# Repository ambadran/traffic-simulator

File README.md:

# traffic-simulator

This Project is a real-life simulation of a traffic camera monitoring for speed, traffic light passing and other violations. Incorporating IOT with a Web App hosting to monitor and control everything.

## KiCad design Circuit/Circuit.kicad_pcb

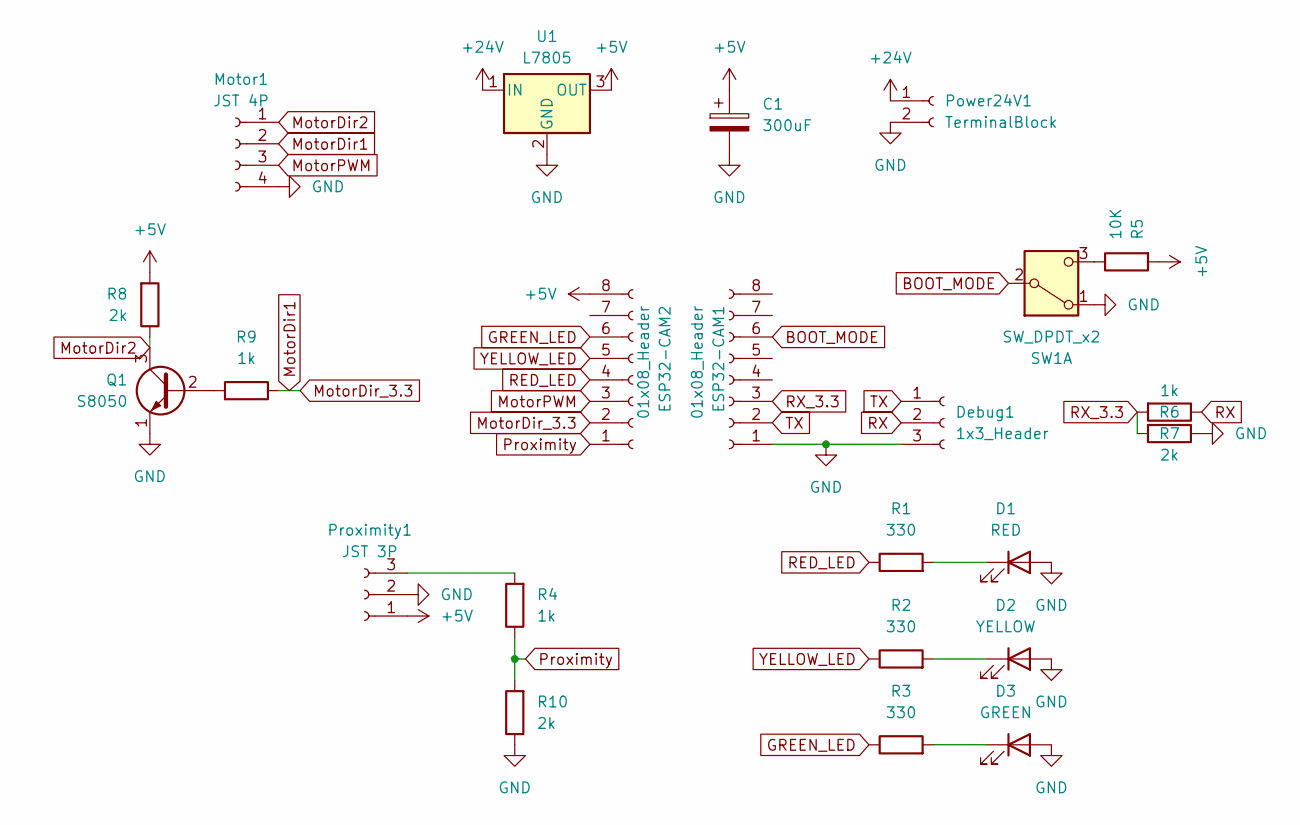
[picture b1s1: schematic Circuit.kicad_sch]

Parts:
C1: 300uF; CP_Radial_D8.0mm_P3.80mm
D1: RED; JST_EH_B2B-EH-A_1x02_P2.50mm_Vertical
D2: YELLOW; JST_EH_B2B-EH-A_1x02_P2.50mm_Vertical
D3: GREEN; JST_EH_B2B-EH-A_1x02_P2.50mm_Vertical
Debug1: 1x3_Header; PinSocket_1x03_P2.54mm_Vertical
ESP32-CAM1, ESP32-CAM2: 01x08_Header; PinSocket_1x08_P2.54mm_Vertical
Motor1: JST 4P; JST_EH_B4B-EH-A_1x04_P2.50mm_Vertical
Power24V1: TerminalBlock; TerminalBlock_bornier-2_P5.08mm
Proximity1: JST 3P; JST_EH_B3B-EH-A_1x03_P2.50mm_Vertical
Q1: S8050; TO-92_Inline_Wide
R1, R2, R3: 330; R_Axial_DIN0207_L6.3mm_D2.5mm_P7.62mm_Horizontal
R4, R6, R9: 1k; R_Axial_DIN0207_L6.3mm_D2.5mm_P7.62mm_Horizontal
R5: 10K; R_Axial_DIN0207_L6.3mm_D2.5mm_P7.62mm_Horizontal
R7, R8, R10: 2k; R_Axial_DIN0207_L6.3mm_D2.5mm_P7.62mm_Horizontal
SW1: SW_DPDT_x2; PinSocket_1x03_P2.54mm_Vertical
U1: L7805; TO-220-3_Vertical

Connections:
+5V: C1.1, ESP32-CAM2.8, Proximity1.1, R5.2, R8.2, U1.3 (OUT)
+24V: Power24V1.1, U1.1 (IN)
BOOT_MODE: ESP32-CAM1.6, SW1.2 (B)
GND: C1.2, D1.2 (A), D2.2 (A), D3.2 (A), Debug1.3, ESP32-CAM1.1, Motor1.4, Power24V1.2, Proximity1.2, Q1.1 (E), R7.1, R10.1, SW1.1 (A), U1.2 (GND)
GREEN_LED: ESP32-CAM2.6, R3.1
MotorDir1: ESP32-CAM2.2, Motor1.2, R9.1
MotorDir2: Motor1.1, Q1.3 (C), R8.1
MotorPWM: ESP32-CAM2.3, Motor1.3
unnamed: D1.1 (K), R1.2
unnamed: D2.1 (K), R2.2
unnamed: D3.1 (K), R3.2
unnamed: Proximity1.3, R4.2
unnamed: Q1.2 (B), R9.2
unnamed: R5.1, SW1.3 (C)
Proximity: ESP32-CAM2.1, R4.1, R10.2
RED_LED: ESP32-CAM2.4, R1.1
RX: Debug1.2, R6.1
RX_3.3: ESP32-CAM1.3, R6.2, R7.2
TX: Debug1.1, ESP32-CAM1.2
YELLOW_LED: ESP32-CAM2.5, R2.1

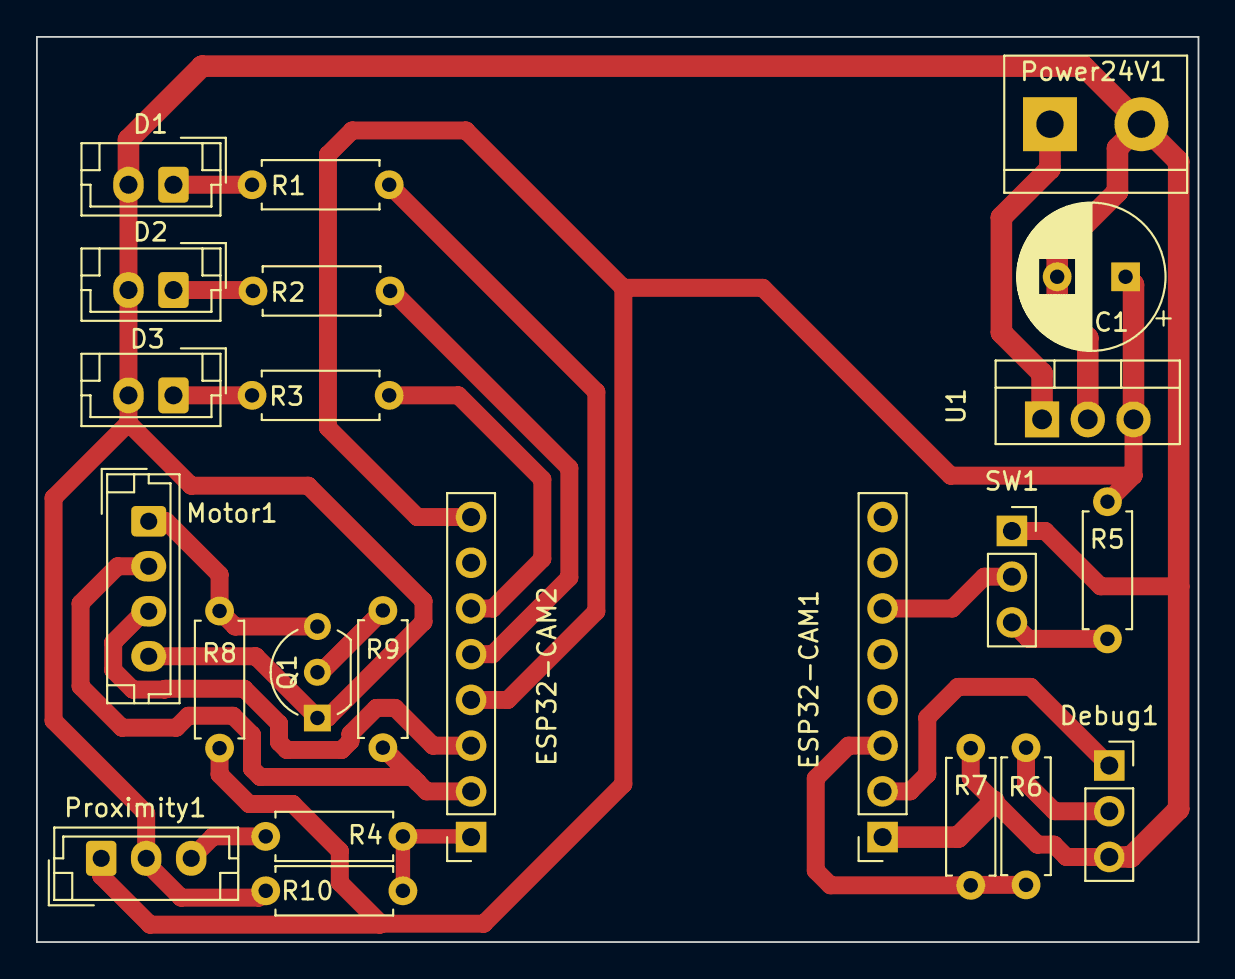
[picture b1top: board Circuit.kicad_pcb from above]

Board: 2 copper layers, 64.5 x 50.3 mm, 23 parts (0 on the bottom side), 20 nets.

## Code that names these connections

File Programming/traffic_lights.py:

'''
Component implementing class to easily control the traffic lights
'''
from machine import Pin, Timer
from time import sleep_ms

class TrafficLight:
    '''
    Class to easily control Traffic light
    '''
    DEFAULT_TIME_IN_BETWEEN = 1000  # 1 second
    RED_LED_IND = 0
    YELLOW_LED_IND = 1
    GREEN_LED_IND = 2

    def __init__(self, red_led_pin_num, yellow_led_pin_num, green_led_pin_num):
        self.red_led = Pin(red_led_pin_num, Pin.OUT)
        self.yellow_led = Pin(yellow_led_pin_num, Pin.OUT)
        self.green_led = Pin(green_led_pin_num, Pin.OUT)

        self.leds = (self.red_led, self.yellow_led, self.green_led)

        self._current_led_ind = 2 # so that first call will light up the red led

    def run(self):
        '''
        runs the Traffic lights
        '''
        #TODO: Apparently on the esp32-cam. Using the Timer invokes the wdt for some reason
        #       I tried timer ids 0-3, all of them invoke this error and reset the chip

        # Guru Meditation Error: Core  1 panic'ed (Interrupt wdt timeout on CPU1).

        # Core  1 register dump:
        # PC      : 0x40092543  PS      : 0x00060034  A0      : 0x80091d21  A1      : 0x3ffb1190
        # A2      : 0x3ffb1238  A3      : 0x3ffb36f4  A4      : 0x3ffb36ec  A5      : 0x00060021
        # A6      : 0x0000abab  A7      : 0xb33fffff  A8      : 0x3ffb36f4  A9      : 0x00000000
        # A10     : 0x00000004  A11     : 0x00060023  A12     : 0x00060021  A13     : 0x3ffbcaa0
        # A14     : 0x00000000  A15     : 0x3ffb3760  SAR     : 0x0000001d  EXCCAUSE: 0x00000006
        # EXCVADDR: 0x00000000  LBEG    : 0x00000000  LEND    : 0x00000000  LCOUNT  : 0x00000000
        # Core  1 was running in ISR context:
        # EPC1    : 0x400d2fcb  EPC2    : 0x00000000  EPC3    : 0x00000000  EPC4    : 0x40092543


        # Backtrace:0x40092540:0x3ffb11900x40091d1e:0x3ffb11b0 0x400d6bc1:0x3ffb11d0 0x400d6c47:0x3ffb1200 0x40083d19:0x3ffb1220 0x4000bfed:0x3ffbca50 0x4011ec92:0x3ffbca60 0x400d2b7d:0x3ffbca80 0x40090574:0x3ffbcaa0


        # Core  0 register dump:
        # PC      : 0x40191d92  PS      : 0x00060734  A0      : 0x800d2b86  A1      : 0x3ffbc300
        # A2      : 0x3ffb4a48  A3      : 0x00060720  A4      : 0x8008a07a  A5      : 0x3ffb0bc0
        # A6      : 0x3ffb1420  A7      : 0x3ffb48a4  A8      : 0x8011ec95  A9      : 0x3ffbc2f0
        # A10     : 0x00000003  A11     : 0x00060723  A12     : 0x00060720  A13     : 0x3ffccce0
        # A14     : 0x00000003  A15     : 0x00060023  SAR     : 0x0000001d  EXCCAUSE: 0x00000006
        # EXCVADDR: 0x00000000  LBEG    : 0x00000000  LEND    : 0x00000000  LCOUNT  : 0x00000000


        # Backtrace:0x40191d8f:0x3ffbc3000x400d2b83:0x3ffbc320 0x40090574:0x3ffbc340

        # ELF file SHA256: 1fb92b2bca51293c


        self.timer = Timer(3) 
        self.timer.init(period=self.DEFAULT_TIME_IN_BETWEEN, mode=Timer.PERIODIC, callback=self.next_light)

    def stop(self):
        '''
        stops the traffic lights
        '''
        self.timer.deinit()

    def next_light(self, t):
        '''
        function to close the previous light and open the next light in order (red, yellow, green)

        param t is for the timer module
        '''
        self.leds[self._current_led_ind].off()

        self._current_led_ind += 1
        if self._current_led_ind > 2:
            self._current_led_ind = 0

        self.leds[self._current_led_ind].on()

    def off(self):
        '''
        closes off all the lights
        '''
        self.red_led.off()
        self.yellow_led.off()
        self.green_led.off()

    def on(self):
        '''
        Turns on all the lights
        '''
        self.red_led.on()
        self.yellow_led.on()
        self.green_led.on()

    def flash_all(self):
        '''
        flashes all leds 3 times with 0.5 second gaps
        '''
        for _ in range(3):
            self.on()
            sleep_ms(500)
            self.off()
            sleep_ms(500)

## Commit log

2024-06-09 added initial folders and files
2024-06-09 added BOM and circuit schematic
2024-06-15 finished circuit and started PCB
2024-06-15 finished PCB
2024-06-15 fixed PCB, started programming
2024-06-15 Wrote most components and web app. pending some fill in the blanks and testing!
2024-06-26 finished Interfacing all sensors and actuators, pending server code
2024-06-27 schematic and PCB modification Done
2024-06-27 further development in server
2024-06-28 finished and tested Main Routine, pending server socket connection testing
2024-06-28 finished Server Side Completely
2024-06-29 added final BOM
